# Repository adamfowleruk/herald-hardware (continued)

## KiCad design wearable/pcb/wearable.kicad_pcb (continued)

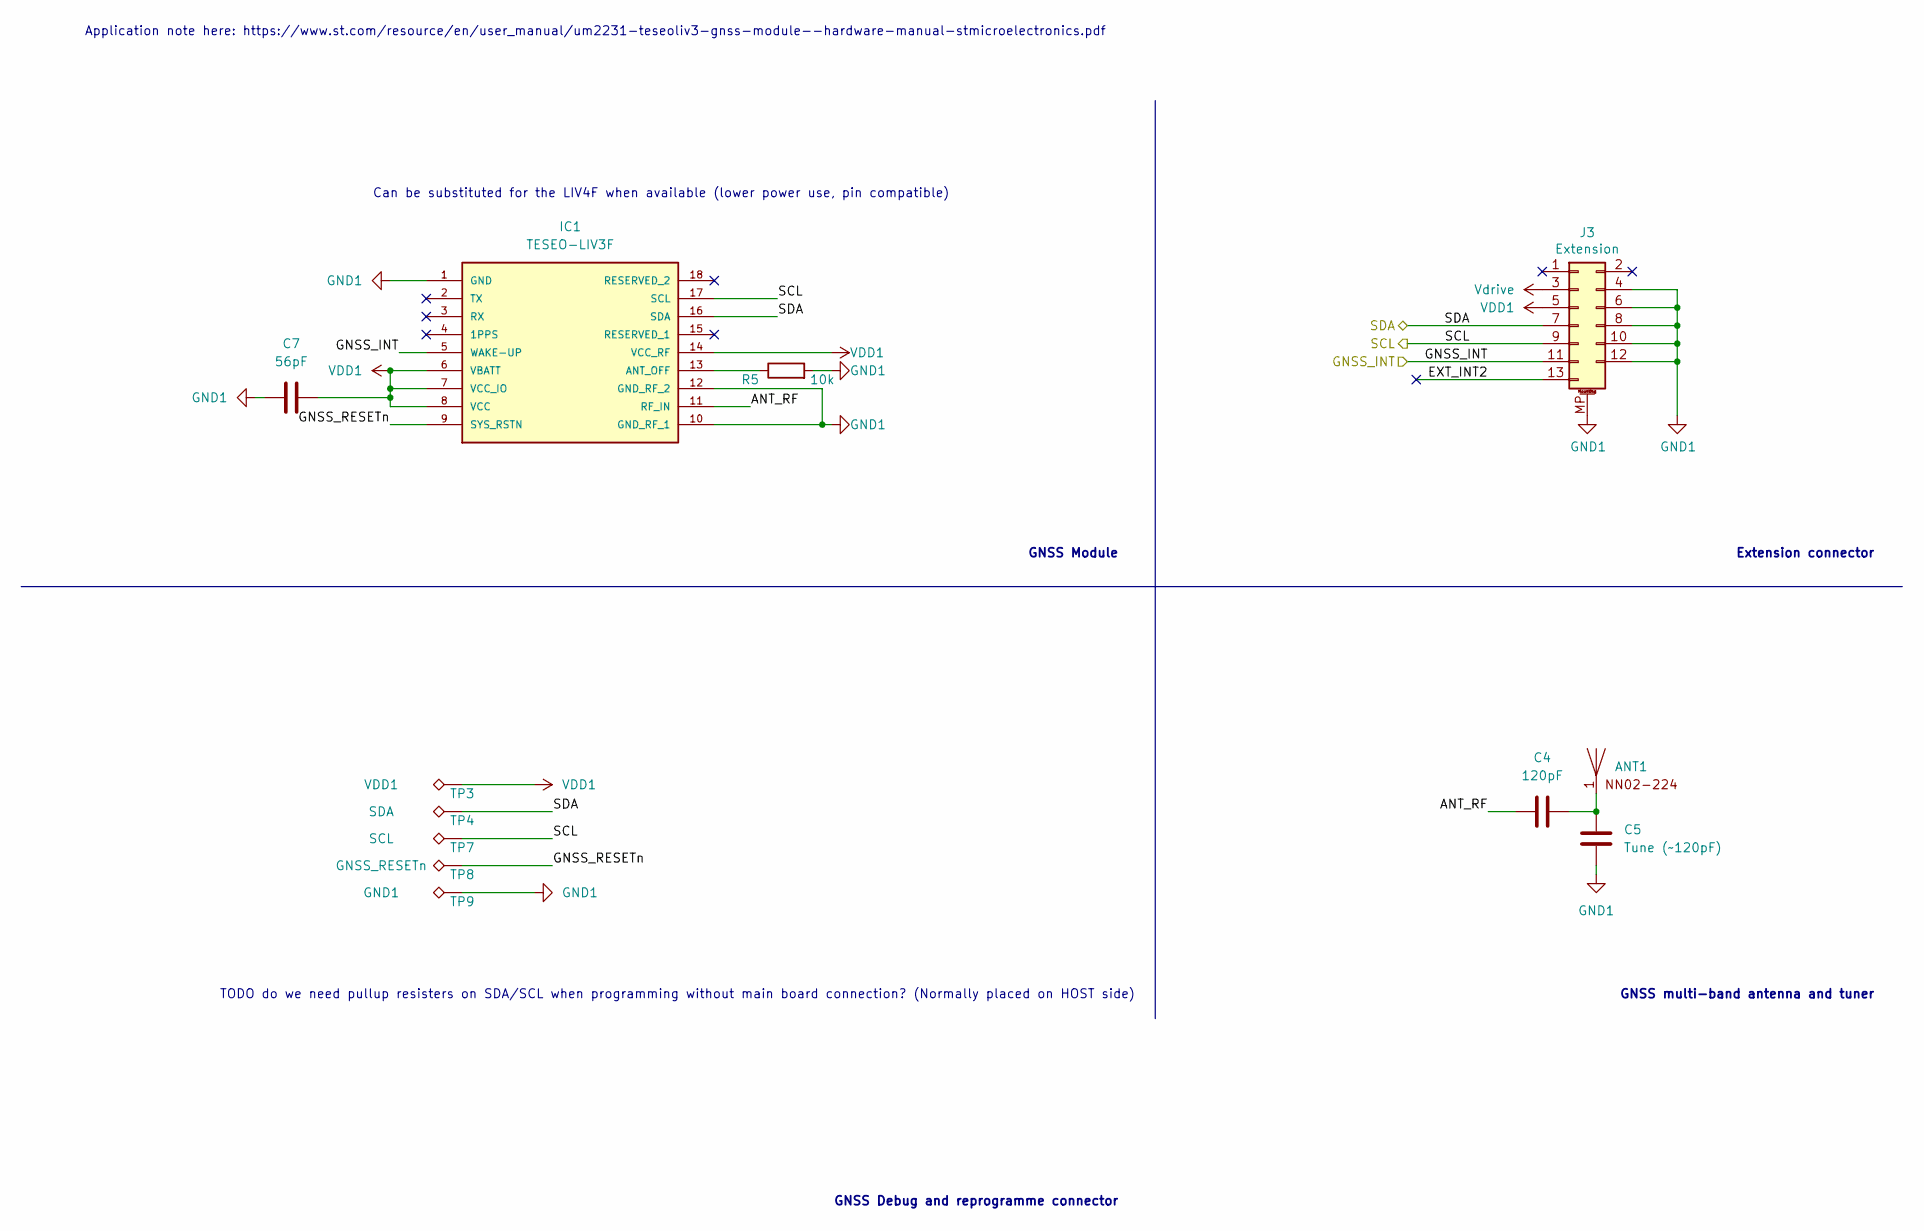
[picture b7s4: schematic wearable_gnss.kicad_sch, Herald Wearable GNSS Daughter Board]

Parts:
ANT1: NN02-224
C4: 120pF; C_0402_1005Metric
C5: Tune (~120pF); C_0402_1005Metric
C7: 56pF; C_0402_1005Metric
IC1: TESEO-LIV3F; SON110P970X1010X230-18N; MOUSER_PART_NUMBER 511-TESEO-LIV3F
J3: Extension; TE_1-2328724-3_2Rows_13Pins_P0.3mm_Horizontal; MPN 1-2328724-3
R5: 10k; R_0402_1005Metric
TP3: VDD1; TestPoint_Pad_D1.0mm
TP4: SDA; TestPoint_Pad_D1.0mm
TP7: SCL; TestPoint_Pad_D1.0mm
TP8: GNSS_RESETn; TestPoint_Pad_D1.0mm
TP9: GND1; TestPoint_Pad_D1.0mm

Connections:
+1V8: J3.3; also elsewhere on the board
/Core Board/EXT_INT1: IC1.5 (WAKE-UP), J3.11; also elsewhere on the board
/Core Board/EXT_INT2: J3.13; also elsewhere on the board
/Core Board/SCL: IC1.17 (SCL), J3.9, TP7.1; also elsewhere on the board
/Core Board/SDA: IC1.16 (SDA), J3.7, TP4.1; also elsewhere on the board
/GNSS Board/ANT_RF: C4.1, IC1.11 (RF_IN)
/GNSS Board/GNSS_RESETn: IC1.9 (SYS_RSTN), TP8.1
GND1: C5.2, C7.2, IC1.1 (GND), IC1.10 (GND_RF_1), IC1.12 (GND_RF_2), J3.4, J3.6, J3.8, J3.10, J3.12, J3.MP (MountPin), R5.2, TP9.1; also elsewhere on the board
unnamed: ANT1.1, C4.2, C5.1
unnamed: IC1.13 (ANT_OFF), R5.1
VDD1: C7.1, IC1.6 (VBATT), IC1.7 (VCC_IO), IC1.8 (VCC), IC1.14 (VCC_RF), J3.5, TP3.1; also elsewhere on the board

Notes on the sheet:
Application note here: https://www.st.com/resource/en/user_manual/um2231-teseoliv3-gnss-module--hardware-manual-stmicroelectronics.pdf
GNSS Debug and reprogramme connector
Can be substituted for the LIV4F when available (lower power use, pin compatible)
Extension connector
GNSS Module
GNSS multi-band antenna and tuner
TODO do we need pullup resisters on SDA/SCL when programming without main board connection? (Normally placed on HOST side)

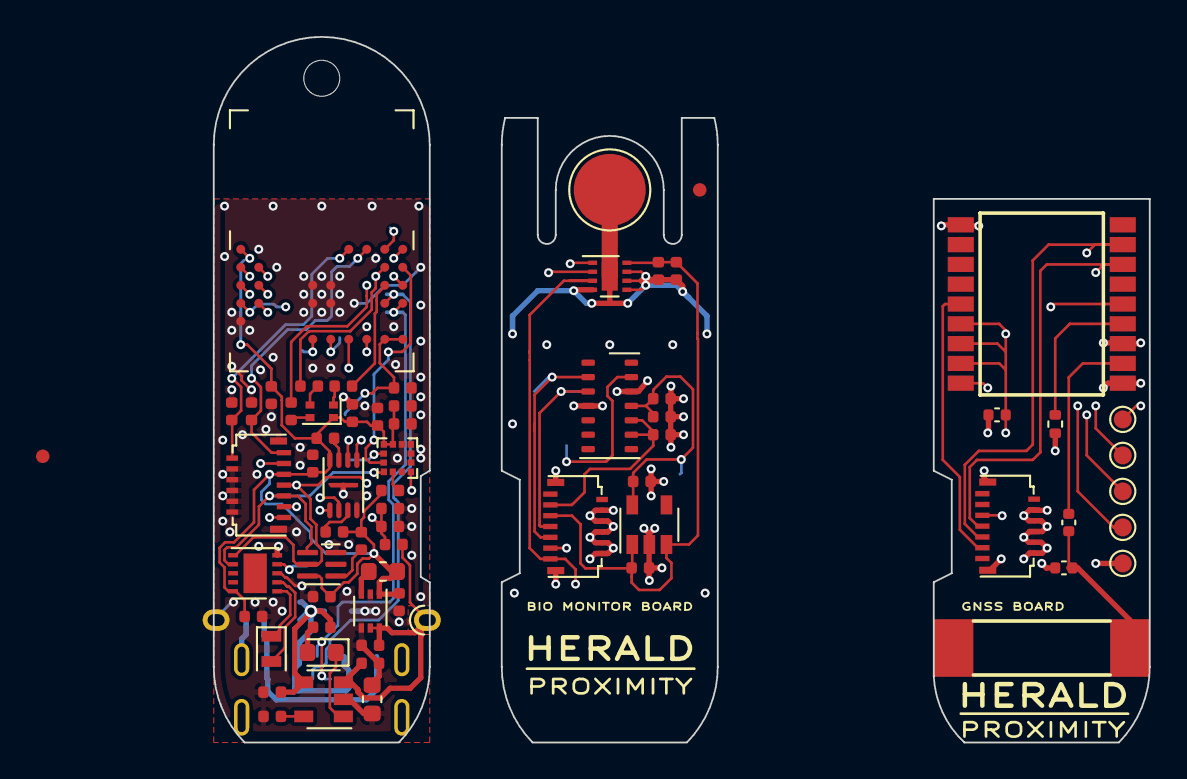
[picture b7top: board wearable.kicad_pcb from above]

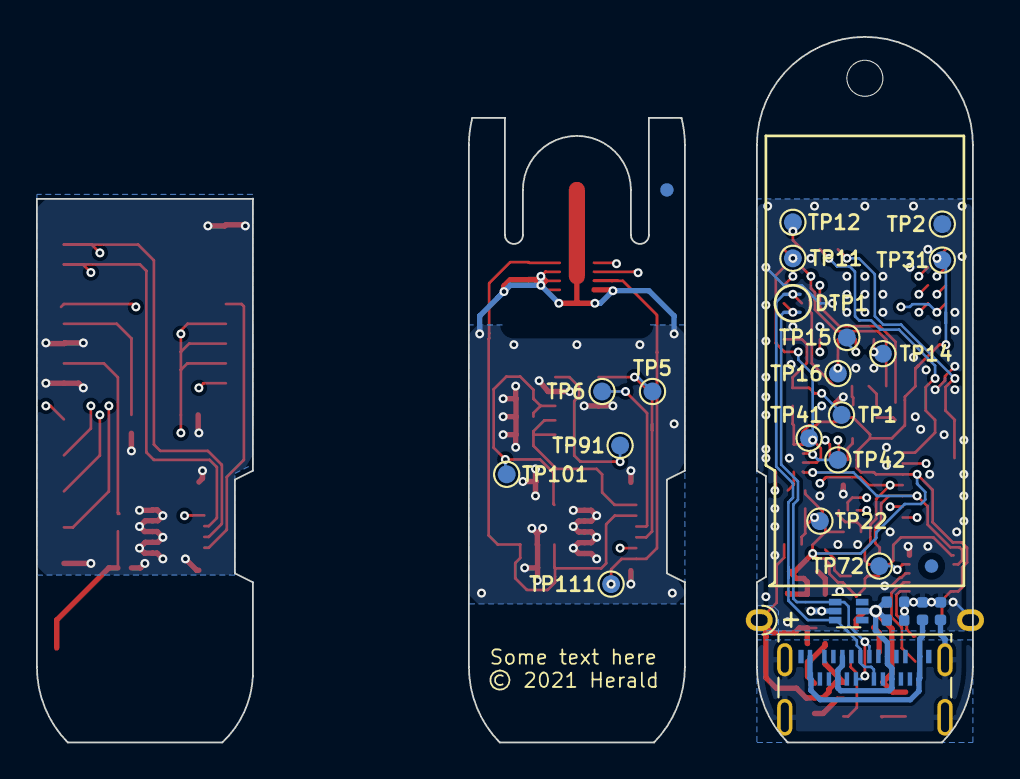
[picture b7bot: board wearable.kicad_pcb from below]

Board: 4 copper layers, 52.0 x 39.2 mm, 94 parts (26 on the bottom side), 47 nets.

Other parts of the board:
J4: Extension; TE_1-2328724-3_2Rows_13Pins_P0.3mm_Horizontal

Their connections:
+1V8: J4.3; also elsewhere on the board
/Core Board/EXT_INT1: J4.11; also elsewhere on the board
/Core Board/SCL: J4.9; also elsewhere on the board
/Core Board/SDA: J4.7; also elsewhere on the board
GND1: J4.4, J4.6, J4.8, J4.10, J4.12, J4.MP (MountPin); also elsewhere on the board
VDD1: J4.5; also elsewhere on the board

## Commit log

2023-07-16 Part of #16. Added Herald Wearable GNSS Daughter Board
    Also upgraded files to KiCAD 6+ (7.0.6) files
    Some missing elements still
2023-07-16 Part of #16. Ferrite Bead symbol link fixed
    Also removed extraneous no connection on EXT_INT2
2023-07-16 Part of #16. Added GNSS PCB layout
    Also added custom footprint for NN02-224 chip antenna.
2023-07-16 Part of #16. Corrected antenna placement
    Ensured minimum 2.5mm ground plane clearance
    Added all component 3D models
2023-09-29 Initial V2 wearable design work.
2023-10-08 Additional V2 wearable design work
2023-10-10 Updated components and PCB layout
2023-10-15 Further V2 routing
2023-10-17 Replaced unavailable I2C chip
2023-10-17 Standard connector almost complete
    Added JLCPCB manufacturer settings to PCB
    Ensured all components are available and Tape and Reel with smallest footprint available
2023-10-17 Completed individual board layouts
2023-10-18 Laid out all boards together
    Added missing models for oscillator, push button, daylight sensor
2023-10-21 Added front connectors on main board
2023-10-21 Added plug connector and routed compute and positioning boards
2023-10-22 All board connectors routed
    Connector positions confirmed
    Extension board dimensions confirmed to not clash
2023-10-22 Corrected 1V8 routing to bio board
2023-10-23 Set wider PCB GND tracks and vias
2023-10-28 First look feedback board
2023-10-29 Added MPN and footprints to display components
2023-10-29 Display board physical layout improvements
2023-10-29 Confirmed display board connectors
2023-10-29 Upgraded flash and corrected XIF placement
2023-11-01 Updated LRA, BOM. Added first 3D model
2023-11-03 Added I2C and I3C notes and additional resistors
2023-11-05 Split main boards out into their own KiCAD files
2023-11-06 Refactoring PCB files
    Moved major boards into their own files.
    Corrected design elements for PCBWay manufacture.
2023-11-09 Added accelerometer to compute module
    Enable low power movement interrupt modes with just the compute module.
2023-11-11 Reworked boards for JLCPCB manufacture
    Slightly larger Vias.
    Added debug pin holes for Beta testing.
2023-11-13 Added Antenna panel and Micro connector boards
    Micro connector uses the nPM1300 PMIC from Nordic Semi.
